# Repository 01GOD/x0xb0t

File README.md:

# x0xb0t
Project Goals:
1. Turning the x0xb0x boards into a sequencer to use with the x0xheart (mainly removing the synth section and making the board smaller). 
2. Converting that sequencer to SMT style PCB design to have a minix0x when used with the x0xheart. 

Note: The x0xheart is basically the synth section of the x0xb0x converted to SMT.

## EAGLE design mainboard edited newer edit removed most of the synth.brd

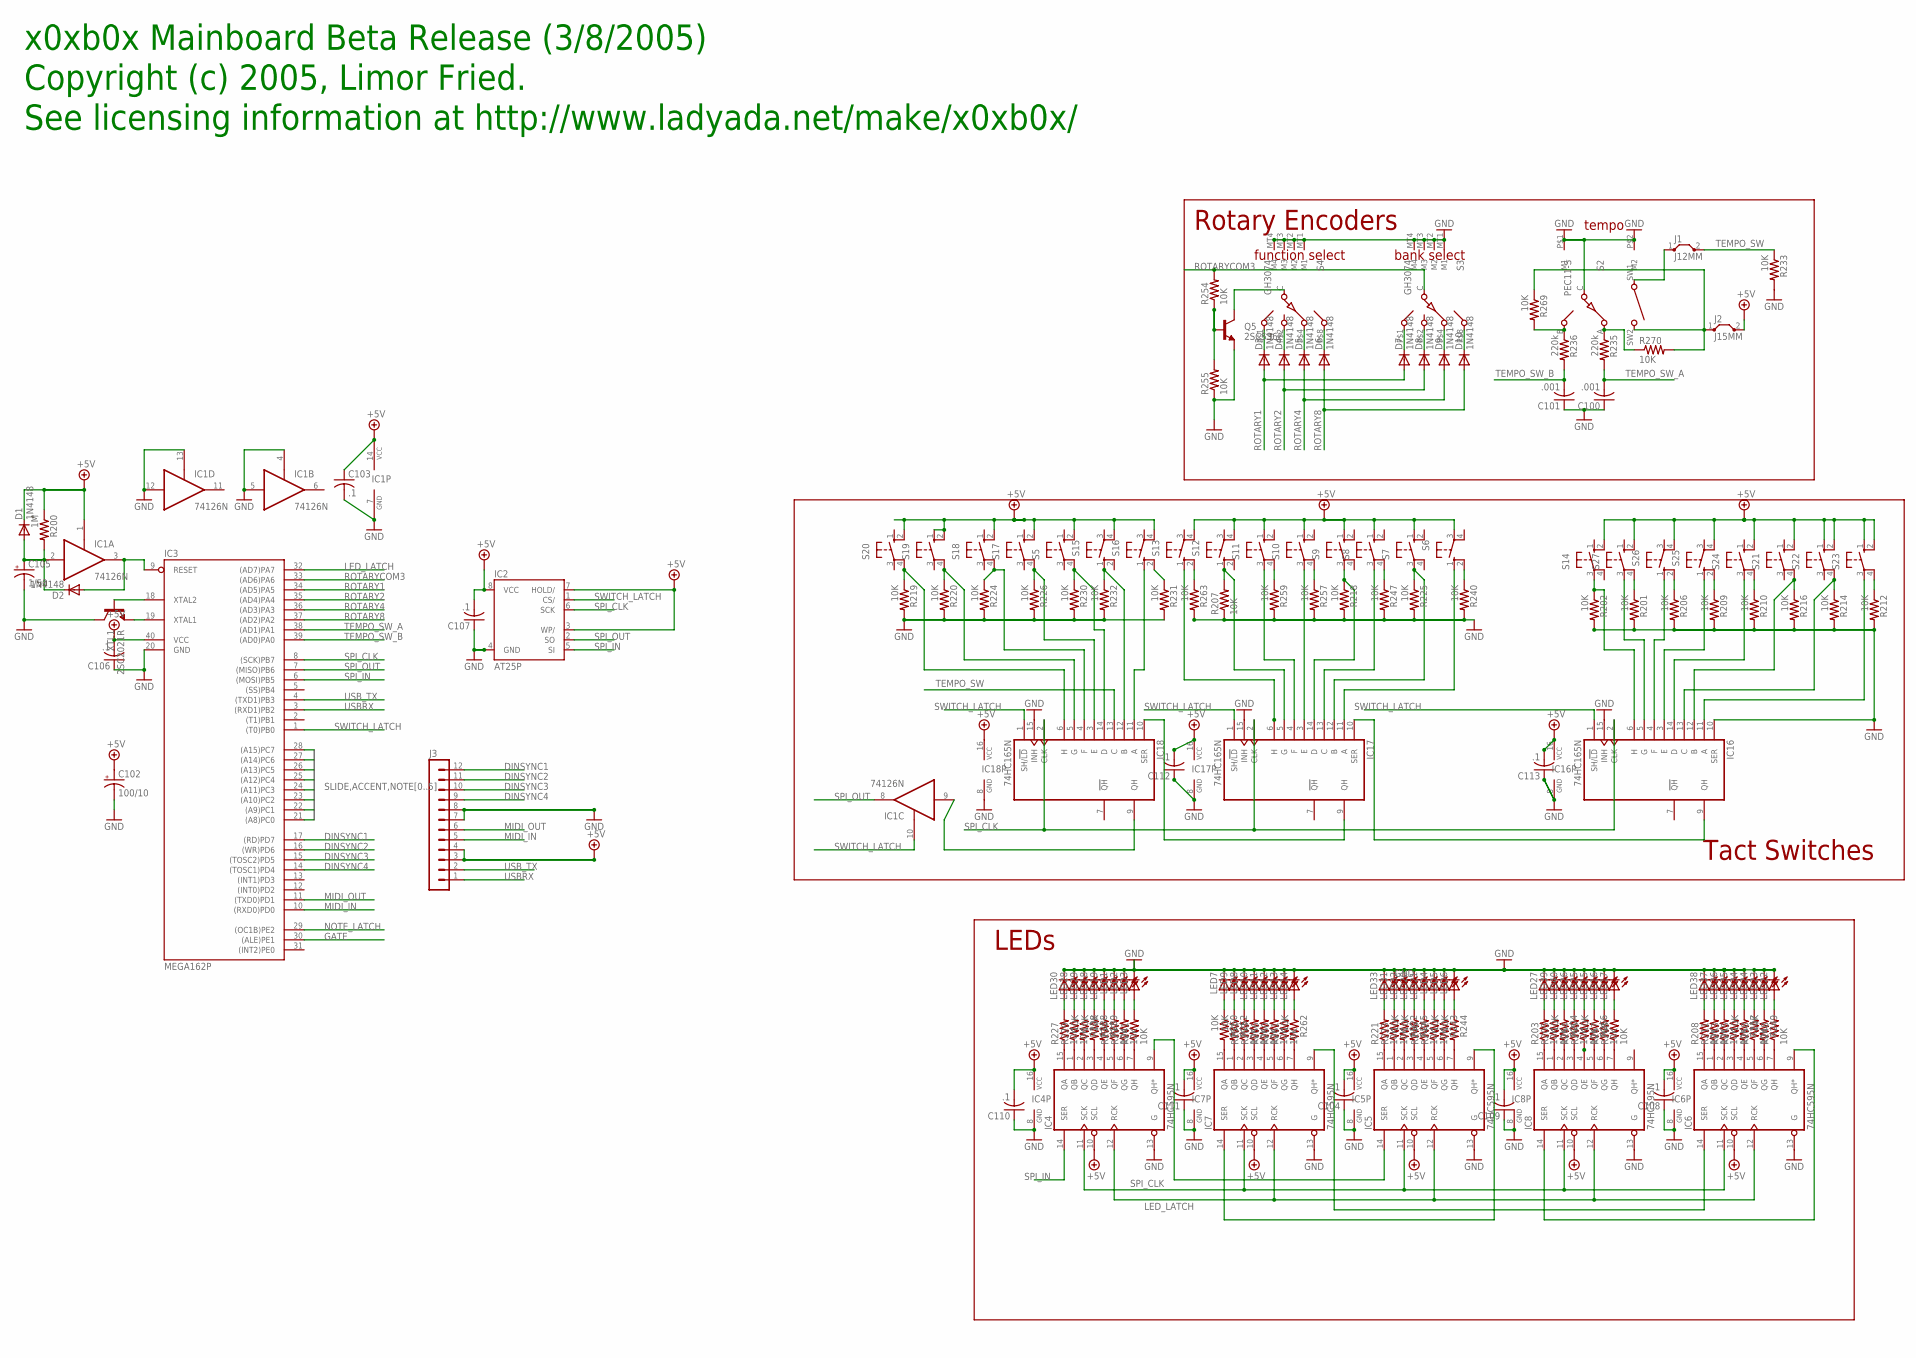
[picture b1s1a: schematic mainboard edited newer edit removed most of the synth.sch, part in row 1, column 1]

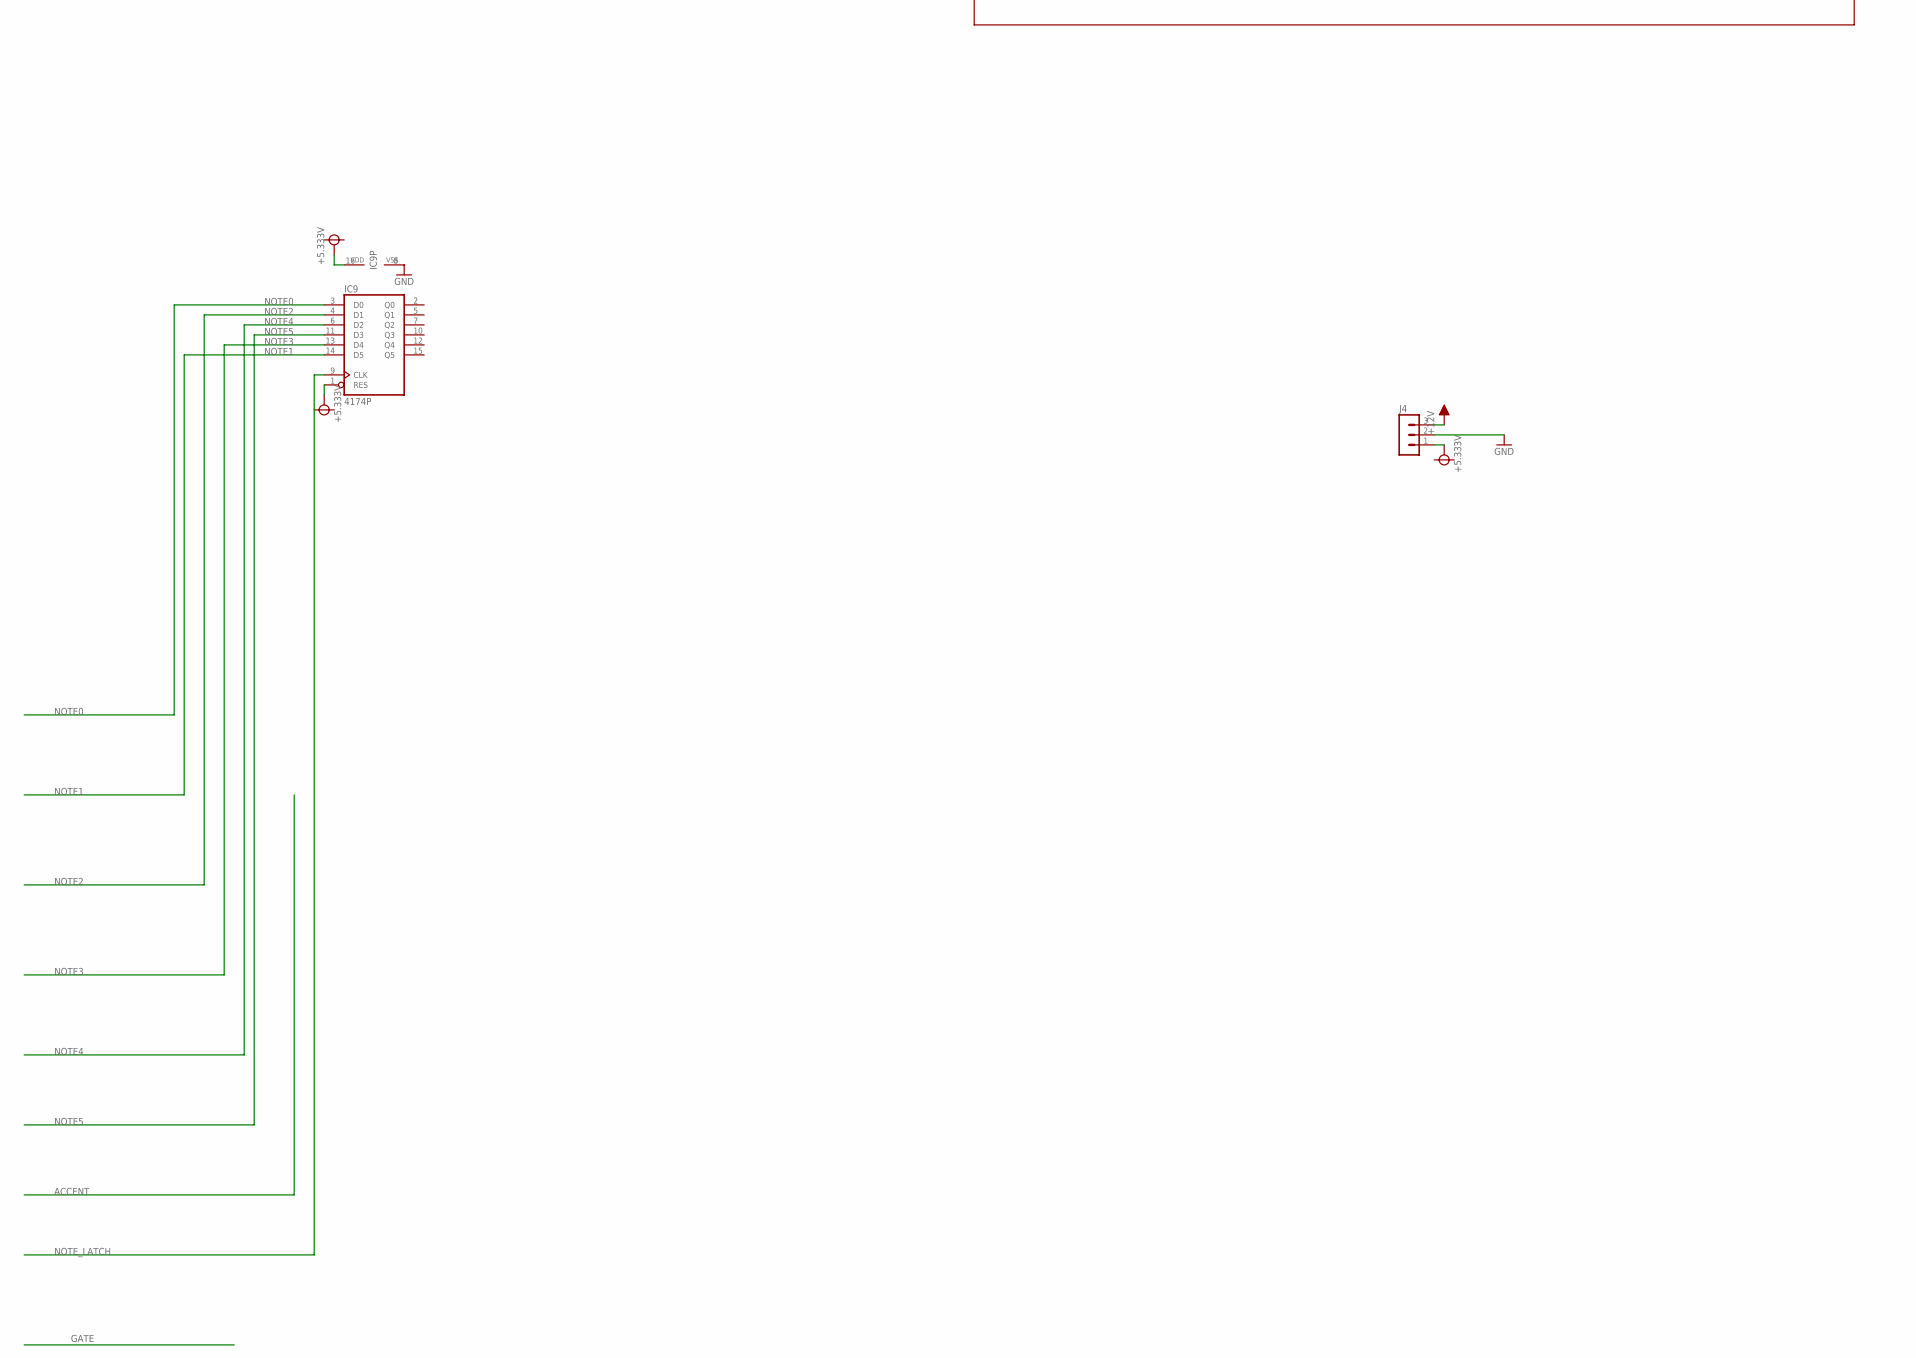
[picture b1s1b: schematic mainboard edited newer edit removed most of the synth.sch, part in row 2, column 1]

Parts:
C100, C101: .001; C050-035X075
C102: 100/10; E5-6
C103, C104, C106, C107, C108, C109, C110, C111, C112, C113: .1; C050H075X075
C105: 1/50; E5-6
D1, D2, D3, D4, D5, D6, D7, D8, D9, D10: 1N4148; DO35-10
IC1: 74126N; DIL14
IC2: AT25P; DIL08
IC3: MEGA162P; DIL40
IC4, IC5, IC6, IC7, IC8: 74HC595N; DIL16
IC9: 4174P; DIL16
IC16, IC17, IC18: 74HC165N; DIL16
J1: J12MM; 12
J2: J15MM; 15
J3: MA12-1
J4: MA03-1
LED1, LED2, LED3, LED4, LED5, LED6, LED7, LED8, LED9, LED10, LED11, LED12, LED13, LED14, LED15, LED16, LED17, LED18, LED19, LED20, LED21, LED22, LED23, LED24, LED25, LED26, LED27, LED28, LED29, LED30, LED31, LED32, LED33, LED34, LED35, LED36, LED37, LED38, LED39, LED40: LED5MM
Q5: 2SC536F
R200: 1M; 0207/5V
R201, R202, R203, R204, R205, R206, R207, R208, R209, R210, R211, R212, R213, R214, R215, R216, R217, R218, R219, R220, R221, R222, R223, R224, R225, R226, R227, R228, R229, R230, R231, R233, R237, R238, R239, R240, R241, R242, R243, R244, R245, R246, R247, R248, R249, R250, R251, R252, R253, R254, R255, R256, R257, R258, R259, R260, R261, R262, R263, R264, R265, R266, R267, R268, R269, R270: 10K; 0207/5V
R232: 10K; 0207/10
R234: 10K; 0207/15
R235, R236: 220k; 0207/5V
S2: PEC11-S
S3, S4: GH3074
S5, S6, S7, S8, S9, S10, S11, S12, S13, S14, S15, S16, S17, S18, S19, S20, S21, S22, S23, S24, S25, S26, S27: 40-XX; B3F-40XX
XTL1: 2SC2021R; 2SC2021

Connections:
+5.333V: IC9.1 (RES), IC9.16 (VDD), J4.1
+5V: C102.+, C103.1, C104.2, C106.2, C107.2, C108.2, C109.2, C110.2, C111.2, C112.2, C113.2, D1.C, IC1.1 (OE), IC1.14 (VCC), IC2.3 (WP/), IC2.7 (HOLD/), IC2.8 (VCC), IC3.40 (VCC), IC4.10 (SCL), IC4.16 (VCC), IC5.10 (SCL), IC5.16 (VCC), IC6.10 (SCL), IC6.16 (VCC), IC7.10 (SCL), IC7.16 (VCC), IC8.10 (SCL), IC8.16 (VCC), IC16.16 (VCC), IC17.16 (VCC), IC18.16 (VCC), J2.2, J3.3, J3.4, R200.1, S5.2 (S1), S6.3, S7.1 (S), S8.1 (S), S9.1 (S), S10.1 (S), S11.1 (S), S12.4 (P1), S13.4 (P1), S14.2 (S1), S15.4 (P1), S16.4 (P1), S17.2 (S1), S18.2 (S1), S19.1 (S), S19.2 (S1), S20.2 (S1), S21.2 (S1), S22.1 (S), S22.2 (S1), S23.1 (S), S23.2 (S1), S24.2 (S1), S25.4 (P1), S26.4 (P1), S27.2 (S1)
+12V: J4.3
ACCENT: IC3.28 ((A15)PC7)
DINSYNC1: IC3.17 ((RD)PD7), J3.12
DINSYNC2: IC3.16 ((WR)PD6), J3.11
DINSYNC3: IC3.15 ((TOSC2)PD5), J3.10
DINSYNC4: IC3.14 ((TOSC1)PD4), J3.9
GATE: IC3.30 ((ALE)PE1)
GND: C100.1, C101.1, C102.-, C103.2, C104.1, C105.-, C106.1, C107.1, C108.1, C109.1, C110.1, C111.1, C112.1, C113.1, IC1.4 (OE), IC1.5 (I), IC1.7 (GND), IC1.12 (I), IC1.13 (OE), IC2.4 (GND), IC3.20 (GND), IC4.8 (GND), IC4.13 (G), IC5.8 (GND), IC5.13 (G), IC6.8 (GND), IC6.13 (G), IC7.8 (GND), IC7.13 (G), IC8.8 (GND), IC8.13 (G), IC9.8 (VSS), IC16.8 (GND), IC16.10 (SER), IC16.15 (INH), IC17.8 (GND), IC17.15 (INH), IC18.8 (GND), IC18.15 (INH), J3.7, J3.8, J4.2, LED1.K (C), LED2.K (C), LED3.K (C), LED4.K (C), LED5.K (C), LED6.K (C), LED7.K (C), LED8.K (C), LED9.K (C), LED10.K (C), LED11.K (C), LED12.K (C), LED13.K (C), LED14.K (C), LED15.K (C), LED16.K (C), LED17.K (C), LED18.K (C), LED19.K (C), LED20.K (C), LED21.K (C), LED22.K (C), LED23.K (C), LED24.K (C), LED25.K (C), LED26.K (C), LED27.K (C), LED28.K (C), LED29.K (C), LED30.K (C), LED31.K (C), LED32.K (C), LED33.K (C), LED34.K (C), LED35.K (C), LED36.K (C), LED37.K (C), LED38.K (C), LED39.K (C), LED40.K (C), Q5.3 (E), R201.2, R202.2, R206.2, R207.1, R209.2, R210.2, R212.2, R214.2, R216.2, R218.2, R219.2, R220.2, R224.2, R225.2, R226.2, R230.2, R231.2, R232.2, R233.2, R240.2, R247.2, R255.1, R257.2, R259.2, R263.2, S2.C, S2.P$1 (M1), S2.P$2 (M2), S3.MT1 (M1), S3.MT2 (M2), S3.MT3 (M3), S3.MT4 (M4), S4.MT1 (M1), S4.MT2 (M2), S4.MT3 (M3), S4.MT4 (M4), XTL1.2 (C)
LED_LATCH: IC3.32 ((AD7)PA7), IC4.12 (RCK), IC5.12 (RCK), IC6.12 (RCK), IC7.12 (RCK), IC8.12 (RCK)
MIDI_IN: IC3.10 ((RXD0)PD0), J3.5
MIDI_OUT: IC3.11 ((TXD0)PD1), J3.6
unnamed: IC7.1 (QB), R252.2
unnamed: Q5.1 (B), R254.1, R255.2
unnamed: R236.1, R269.2, S2.B
unnamed: IC4.7 (QH), R241.1
unnamed: IC1.9 (I), IC18.9 (QH)
unnamed: C105.+, D1.A, D2.C, IC1.2 (I), R200.2
unnamed: IC4.6 (QG), R237.1
unnamed: IC17.5 (G), R207.2, S12.1 (S)
unnamed: LED6.A, R244.1
unnamed: LED7.A, R250.1
unnamed: R257.1, S10.4 (P1)
unnamed: IC17.14 (D), R218.1, S9.3
unnamed: IC17.13 (C), S8.3
unnamed: IC17.12 (B), R225.1, S7.3
unnamed: R259.1, S11.4 (P1)
unnamed: IC18.14 (D), R230.1, S5.4 (P1)
unnamed: D3.C, S4.P$1 (1)
unnamed: IC18.12 (B), R232.1, S15.1 (S)
unnamed: R206.1, S26.2 (S1)
unnamed: IC16.5 (G), S27.3
unnamed: IC17.9 (QH), IC18.10 (SER)
unnamed: IC18.4 (F), R224.1, S18.4 (P1)
unnamed: IC17.4 (F), S11.3
unnamed: D4.C, S4.P$2 (2)
unnamed: R209.1, S25.2 (S1)
unnamed: IC4.5 (QF), R234.1
unnamed: IC5.9 (QH*), IC7.14 (SER)
unnamed: IC5.6 (QG), R243.2
unnamed: IC5.7 (QH), R244.2
unnamed: IC5.5 (QF), R242.1
unnamed: IC7.15 (QA), R250.2
unnamed: IC7.2 (QC), R251.1
unnamed: LED1.A, R234.2
unnamed: LED2.A, R237.2
unnamed: IC7.3 (QD), R253.1
unnamed: IC7.4 (QE), R256.1
unnamed: LED14.A, R262.1
unnamed: IC8.3 (QD), R264.1
unnamed: IC8.6 (QG), R267.1
unnamed: IC8.7 (QH), R268.1
unnamed: IC8.5 (QF), R266.2
unnamed: IC5.1 (QB), R223.1
unnamed: IC8.4 (QE), R265.1
unnamed: IC5.2 (QC), R222.2
unnamed: IC5.15 (QA), R221.1
unnamed: IC5.4 (QE), R246.1
unnamed: IC5.3 (QD), R245.2
unnamed: IC4.3 (QD), R238.2
unnamed: IC4.4 (QE), R239.2
unnamed: IC4.1 (QB), R229.1
unnamed: IC7.6 (QG), R261.1
unnamed: IC7.7 (QH), R262.2
unnamed: IC7.5 (QF), R260.1
unnamed: IC4.2 (QC), R228.2
unnamed: IC4.15 (QA), R227.1
unnamed: IC8.15 (QA), R203.1
unnamed: IC8.1 (QB), R205.1
unnamed: IC8.2 (QC), R204.2
unnamed: IC6.15 (QA), R208.1
unnamed: IC6.1 (QB), R211.1
unnamed: IC6.2 (QC), R213.1
unnamed: IC6.3 (QD), R215.1
unnamed: IC6.4 (QE), R217.2
unnamed: IC6.7 (QH), R248.1
unnamed: IC6.6 (QG), R249.2
unnamed: IC6.5 (QF), R258.1
unnamed: IC16.9 (QH), IC17.10 (SER)
unnamed: IC16.13 (C), R214.1, S22.4 (P1)
unnamed: R210.1, S24.4 (P1)
unnamed: IC16.11 (A), S23.3
unnamed: IC16.4 (F), S26.1 (S)
unnamed: IC18.6 (H), R219.1, S20.4 (P1)
unnamed: IC16.12 (B), R216.1, S21.4 (P1)
unnamed: R240.1, S6.2 (S1)
unnamed: IC16.14 (D), S24.3
unnamed: R201.1, S27.4 (P1)
unnamed: R235.1, R270.1, S2.A
unnamed: R212.1, S23.4 (P1)
unnamed: LED9.A, R252.1
unnamed: LED10.A, R253.2
unnamed: LED11.A, R256.2
unnamed: LED12.A, R260.2
unnamed: IC18.5 (G), R220.1, S19.4 (P1)
unnamed: R231.1, S16.2 (S1)
unnamed: IC16.6 (H), R202.1, S14.3
unnamed: R263.1, S13.2 (S1)
unnamed: Q5.2 (C), S4.C
unnamed: IC17.6 (H), S13.1 (S)
unnamed: IC18.3 (E), R226.1, S17.4 (P1)
unnamed: IC17.3 (E), S10.3
unnamed: LED16.A, R267.2
unnamed: IC17.11 (A), S6.1 (S)
unnamed: IC18.11 (A), S16.1 (S)
unnamed: IC16.3 (E), S25.1 (S)
unnamed: R247.1, S8.4 (P1)
unnamed: LED3.A, R241.2
unnamed: LED4.A, R242.2
unnamed: LED5.A, R243.1
unnamed: LED15.A, R266.1
unnamed: LED8.A, R251.2
unnamed: LED13.A, R261.2
unnamed: IC4.9 (QH*), IC5.14 (SER)
unnamed: IC6.14 (SER), IC7.9 (QH*)
unnamed: IC6.9 (QH*), IC8.14 (SER)
unnamed: LED17.A, R268.2
unnamed: LED18.A, R238.1
unnamed: LED19.A, R239.1
unnamed: LED20.A, R245.1
unnamed: LED21.A, R246.2
unnamed: LED22.A, R248.2
unnamed: LED23.A, R249.1
unnamed: LED24.A, R258.2
unnamed: LED25.A, R265.2
unnamed: LED26.A, R264.2
unnamed: LED27.A, R203.2
unnamed: LED28.A, R229.2
unnamed: LED29.A, R228.1
unnamed: LED30.A, R227.2
unnamed: LED31.A, R223.2
unnamed: LED32.A, R222.1
unnamed: LED33.A, R221.2
unnamed: LED34.A, R217.1
unnamed: LED35.A, R215.2
unnamed: LED36.A, R213.2
unnamed: LED37.A, R211.2
unnamed: LED38.A, R208.2
unnamed: LED39.A, R205.2
unnamed: LED40.A, R204.1
unnamed: D2.A, IC1.3 (O), IC3.9 (RESET)
unnamed: D5.C, S4.P$4 (4)
unnamed: D6.C, S4.P$8 (8)
unnamed: D7.C, S3.P$1 (1)
unnamed: D8.C, S3.P$2 (2)
unnamed: D9.C, S3.P$4 (4)
unnamed: D10.C, S3.P$8 (8)
unnamed: J1.1, S2.SW1
unnamed: J2.1, R269.1, R270.2, S2.SW2
unnamed: IC3.18 (XTAL2), XTL1.3 (B)
NOTE0: IC3.21 ((A8)PC0), IC9.3 (D0)
NOTE1: IC3.22 ((A9)PC1), IC9.14 (D5)
NOTE2: IC3.23 ((A10)PC2), IC9.4 (D1)
NOTE3: IC3.24 ((A11)PC3), IC9.13 (D4)
NOTE4: IC3.25 ((A12)PC4), IC9.6 (D2)
NOTE5: IC3.26 ((A13)PC5), IC9.11 (D3)
NOTE_LATCH: IC3.29 ((OC1B)PE2), IC9.9 (CLK)
ROTARY1: D3.A, D7.A, IC3.34 ((AD5)PA5)
ROTARY2: D4.A, D8.A, IC3.35 ((AD4)PA4)
ROTARY4: D5.A, D9.A, IC3.36 ((AD3)PA3)
ROTARY8: D6.A, D10.A, IC3.37 ((AD2)PA2)
ROTARYCOM3: IC3.33 ((AD6)PA6), R254.2, S3.C
SLIDE: IC3.27 ((A14)PC6)
SPI_CLK: IC2.6 (SCK), IC3.8 ((SCK)PB7), IC4.11 (SCK), IC5.11 (SCK), IC6.11 (SCK), IC7.11 (SCK), IC8.11 (SCK), IC16.2 (CLK), IC17.2 (CLK), IC18.2 (CLK)
SPI_IN: IC2.5 (SI), IC3.6 ((MOSI)PB5), IC4.14 (SER)
SPI_OUT: IC1.8 (O), IC2.2 (SO), IC3.7 ((MISO)PB6)
SWITCH_LATCH: IC1.10 (OE), IC2.1 (CS/), IC3.1 ((T0)PB0), IC16.1 (SH/!LD), IC17.1 (SH/!LD), IC18.1 (SH/!LD)
TEMPO_SW: IC18.13 (C), J1.2, R233.1
TEMPO_SW_A: C100.2, IC3.38 ((AD1)PA1), R235.2
TEMPO_SW_B: C101.2, IC3.39 ((AD0)PA0), R236.2
USBRX: IC3.3 ((RXD1)PB2), J3.1
USB_TX: IC3.4 ((TXD1)PB3), J3.2
XTL1: IC3.19 (XTAL1), XTL1.1 (E)

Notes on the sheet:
LEDs
Tact Switches
tempo
function select
bank select
Rotary Encoders
Copyright (c) 2005, Limor Fried.
See licensing information at http://www.ladyada.net/make/x0xb0x/
x0xb0x Mainboard Beta Release (3/8/2005)

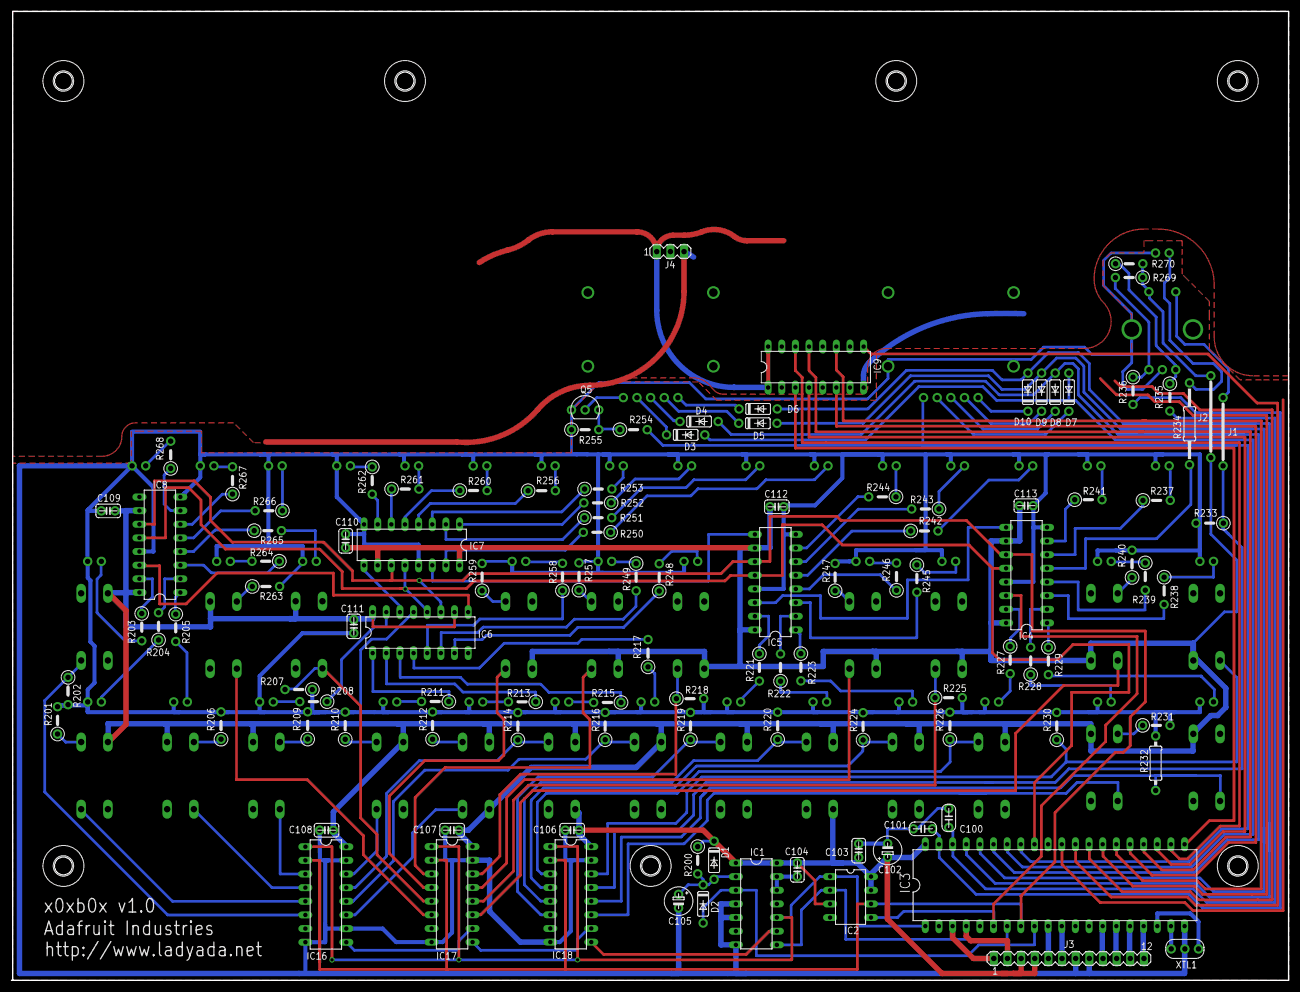
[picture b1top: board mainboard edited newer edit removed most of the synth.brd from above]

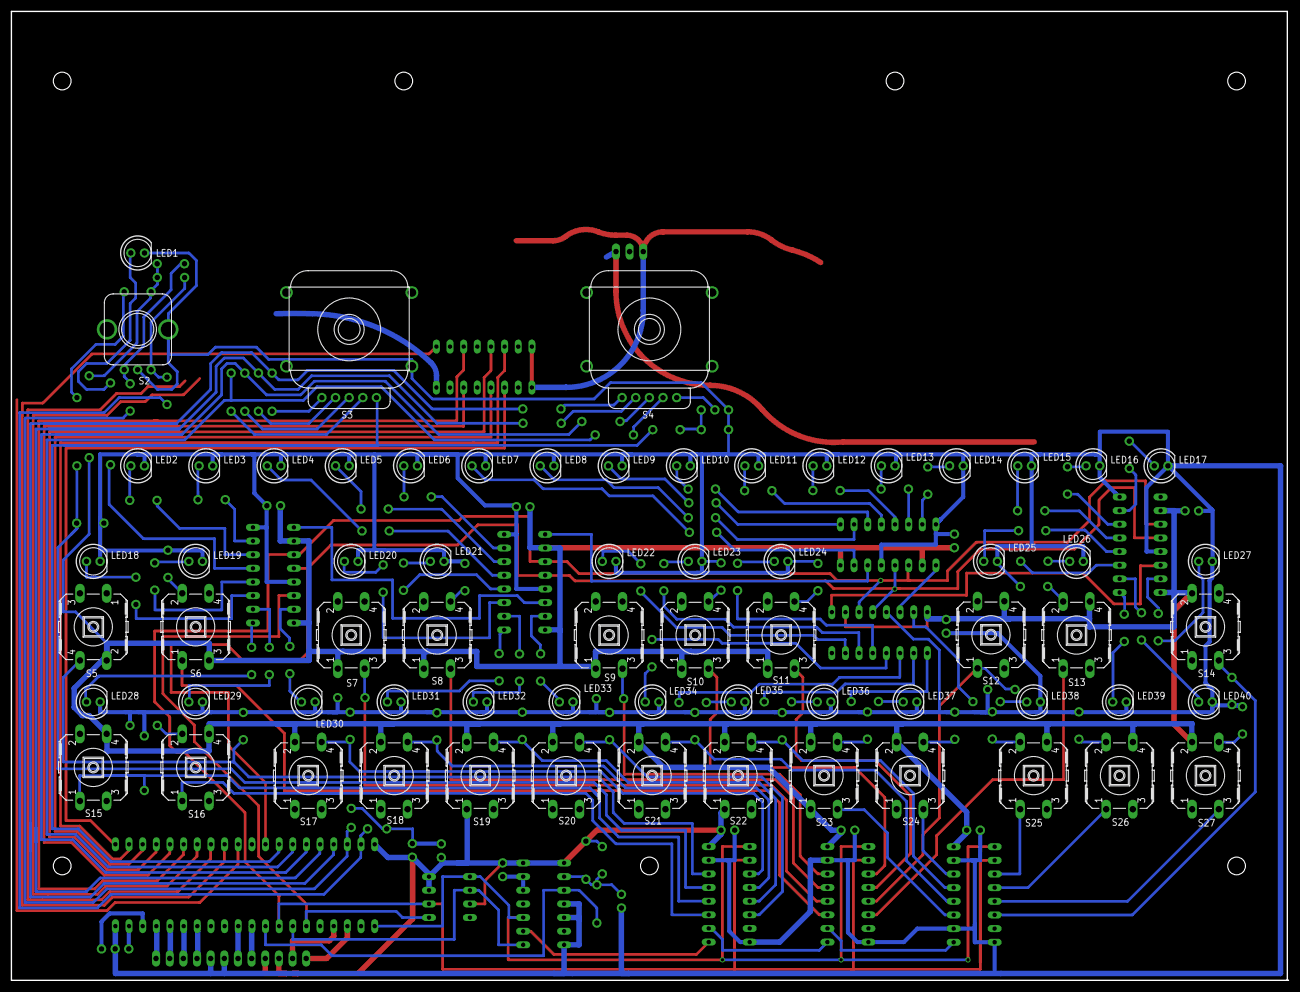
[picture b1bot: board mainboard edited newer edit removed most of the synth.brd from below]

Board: 2 copper layers, 237.5 x 180.3 mm, 186 parts (66 on the bottom side), 170 nets.

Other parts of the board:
U$2, U$23, U$24, U$25, U$27, U$28, U$29: 1,3

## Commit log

2019-10-23 Removed most of the synth section.
    Still some wires and some airwires to handle. (Carefully) Hoping a highly skilled EE will do that soon.
